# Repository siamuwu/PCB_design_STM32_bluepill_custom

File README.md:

# Custom STM32 Development Board

This project is a custom-designed 2-layer PCB based on the STM32 Blue Pill development board. The goal was to build a compact and reliable microcontroller board with proper power regulation and a USB interface.

### Features
- UART and I²C communication interfaces.
- USB Type-B connector.
- Bootloader pins for programming and configuration.
- Serial Wire Debug (SWD) interface for debugging and programming.
- Power regulation and filtering circuits.

### Practical Applications
This board can serve as a general-purpose microcontroller platform for developing and testing embedded systems. It can be used to:
- Interface with sensors and modules through I²C and UART.
- Read sensor data and control external devices.
- Develop and test custom embedded firmware.
- Debug and troubleshoot microcontroller-based projects using SWD.
- Build the control unit for small electronics and automation projects.

### What I Learned
- Designing and routing 2-layer PCBs.
- Working with basic communication protocols such as UART and I²C.
- Using copper polygon pours for PCB connections.
- Selecting suitable capacitors especially for oscillator circuits.
- Understanding power regulation and filtering.
- Using PI filters with ferrite beads, bulk capacitors and decoupling capacitors.
- Designing PCB through KiCAD.

### Learning Reference
I learned the design process by following **Phil's Lab** on YouTube. I used his schematics and PCB design as a learning reference. I learned his routing techniques and design preferences then applied them while routing my own PCB and thus made my first PCB project on KiCAD.

For schematics and pcb check the files 

## Images:
## Schematic View:
### LDO Configuration:

### Layout of STM32F103C8T6:

### PCB Design:

### Top View:

### Bottom View

### Angled View

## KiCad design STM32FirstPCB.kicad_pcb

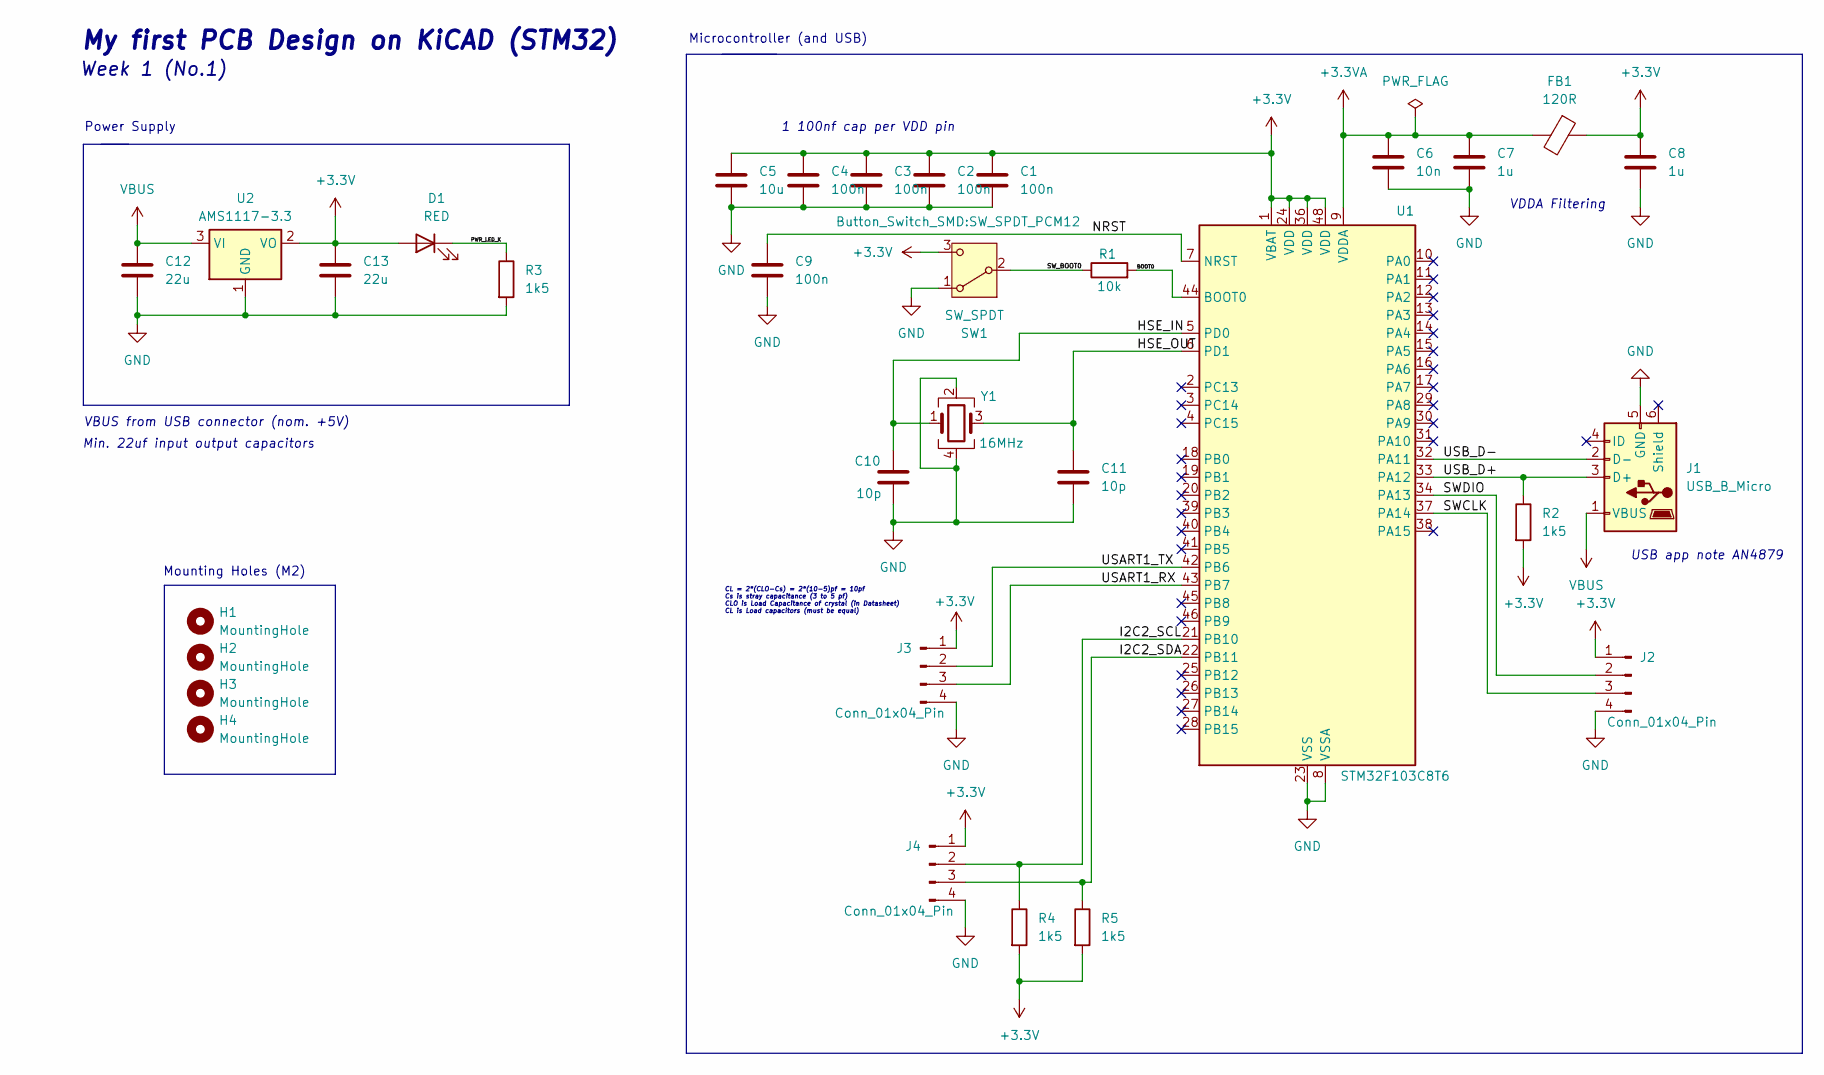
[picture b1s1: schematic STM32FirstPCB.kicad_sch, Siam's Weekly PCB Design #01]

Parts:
C1, C2, C3, C4: 100n; C_0402_1005Metric
C5: 10u; C_0201_0603Metric
C6: 10n; C_0402_1005Metric
C7, C8: 1u; C_01005_0402Metric
C9: 100n; C_01005_0402Metric
C10, C11: 10p; C_01005_0402Metric
C12, C13: 22u; C_0805_2012Metric
D1: RED; LED_0201_0603Metric
FB1: 120R; L_0201_0603Metric
H1, H2, H3, H4: MountingHole; MountingHole_2.2mm_M2
J1: USB_B_Micro; USB_Micro-B_Wuerth_629105150521
J2, J3, J4: Conn_01x04_Pin; PinHeader_1x04_P2.54mm_Vertical
R1: 10k; R_0402_1005Metric
R2, R3, R4, R5: 1k5; R_0402_1005Metric
SW1: SW_SPDT; SW_SPDT_PCM12
U1: STM32F103C8T6; LQFP-48_7x7mm_P0.5mm
U2: AMS1117-3.3; SOT-223-3_TabPin2
Y1: 16MHz; Crystal_SMD_3225-4Pin_3.2x2.5mm

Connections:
+3.3V: C1.1, C2.1, C3.1, C4.1, C5.1, C8.1, C13.1, D1.2 (A), FB1.1, J2.1, J3.1, J4.1, R2.2, R4.2, R5.2, SW1.3 (C), U1.1 (VBAT), U1.24 (VDD), U1.36 (VDD), U1.48 (VDD), U2.2 (VO)
+3.3VA: C6.1, C7.1, FB1.2, U1.9 (VDDA)
/BOOT0: R1.2, U1.44 (BOOT0)
/HSE_IN: C10.1, U1.5 (PD0), Y1.1
/HSE_OUT: C11.1, U1.6 (PD1), Y1.3
/I2C2_SCL: J4.2, R4.1, U1.21 (PB10)
/I2C2_SDA: J4.3, R5.1, U1.22 (PB11)
/NRST: C9.1, U1.7 (NRST)
/PWR_LED_K: D1.1 (K), R3.1
/SWCLK: J2.3, U1.37 (PA14)
/SWDIO: J2.2, U1.34 (PA13)
/SW_BOOT0: R1.1, SW1.2 (B)
/USART1_RX: J3.3, U1.43 (PB7)
/USART1_TX: J3.2, U1.42 (PB6)
/USB_D+: J1.3 (D+), R2.1, U1.33 (PA12)
/USB_D-: J1.2 (D-), U1.32 (PA11)
GND: C1.2, C2.2, C3.2, C4.2, C5.2, C6.2, C7.2, C8.2, C9.2, C10.2, C11.2, C12.2, C13.2, J1.5 (GND), J2.4, J3.4, J4.4, R3.2, SW1.1 (A), U1.8 (VSSA), U1.23 (VSS), U1.35 (VSS), U1.47 (VSS), U2.1 (GND), Y1.2, Y1.4
VBUS: C12.1, J1.1 (VBUS), U2.3 (VI)

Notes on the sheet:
CL = 2*(CLO-Cs) = 2*(10-5)pf = 10pf Cs is stray capacitance (3 to 5 pf) CLO is Load Capacitance of crystal (in Datasheet) CL is Load capacitors (must be equal)
VDDA Filtering
USB app note AN4879
Power Supply
Week 1 (No.1)
Microcontroller (and USB)
Mounting Holes (M2)
Min. 22uf input output capacitors
My first PCB Design on KiCAD (STM32)
VBUS from USB connector (nom. +5V)
1 100nf cap per VDD pin

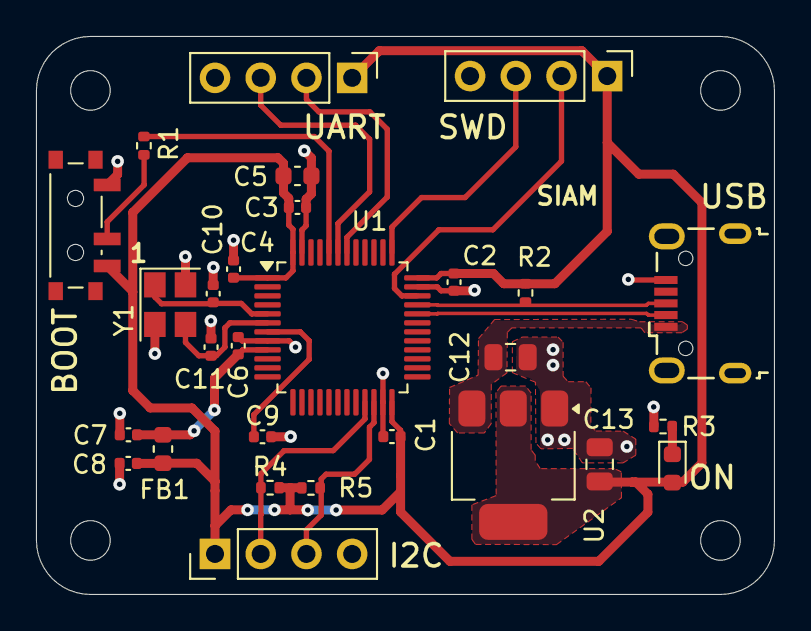
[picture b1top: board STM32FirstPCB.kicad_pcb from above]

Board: 2 copper layers, 41.0 x 31.0 mm, 32 parts (0 on the bottom side), 18 nets.

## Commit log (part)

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2026-04-14 Update .gitignore to exclude backup and junk files
    Add patterns to ignore KiCad backup, autosave, and OS junk files.
2026-04-14 Images of the PCB
2026-04-14 Rename Screenshot 2026-04-14 142731.png to top.png
2026-04-14 Rename Screenshot 2026-04-14 142853.png to angled_view.png
2026-04-14 Rename Screenshot 2026-04-14 142754.png to bottom.png
2026-04-14 Rename top.png to Images/top.png
2026-04-14 Rename angled_view.png to Images/angled_view.png
2026-04-14 Rename bottom.png to Images/bottom.png
2026-04-14 Update README with image references
    Added image references to the README for better visualization.
2026-04-14 Rename STM32FirstPCB.kicad_pro to Schematic_PCB_files/STM32FirstPCB.kicad_pro
2026-04-14 Rename STM32FirstPCB.kicad_pcb to Schematic_PCB_files/STM32FirstPCB.kicad_pcb
2026-04-14 Rename STM32FirstPCB.drl to Schematic_PCB_files/STM32FirstPCB.drl
2026-04-14 Rename STM32FirstPCB.kicad_sch to Schematic_PCB_files/STM32FirstPCB.kicad_sch
2026-04-14 Rename 629105150521 (rev1).stp to Schematic_PCB_files/629105150521 (rev1).stp
2026-04-14 Rename STM32FirstPCB.kicad_prl to Schematic_PCB_files/STM32FirstPCB.kicad_prl
2026-04-14 Rename STM32FirstPCB.kicad_sch-bak to Schematic_PCB_files/STM32FirstPCB.kicad_sch-bak
